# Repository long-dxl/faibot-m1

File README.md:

# Faibot M1

An open mobile robot with two arms and a lifting column, built for university robotics labs. This repository holds its CAD, simulation model, Python SDK, wiring diagrams and assembly guide.

**Status:** design v0.5, before the first engineering build. No physical robot has been assembled yet; everything here is checked in simulation and against the CAD.

## Simulation demos

Three lab tasks, played at 2× speed (60 fps). Each task was measured on 20 randomised seeds before recording.

| Sorting | Pick & place | Opening & closing |
| --- | --- | --- |
|  |  |  |
| Both arms pick at the same time and the base carries the objects to the tray. A zone lock keeps only one arm inside the tray area at a time. [MP4](media/video/m1-sorting-60fps-2x.mp4) · [WebM](media/video/m1-sorting-60fps-2x.webm) | Objects are picked from the table and placed in a box while the base moves between them. [MP4](media/video/m1-pick_place-60fps-2x.mp4) · [WebM](media/video/m1-pick_place-60fps-2x.webm) | The drawer is pulled open, an object is placed inside and the drawer is closed. At the fridge, the right arm opens the door and the left arm takes the can out. [MP4](media/video/m1-open_close-60fps-2x.mp4) · [WebM](media/video/m1-open_close-60fps-2x.webm) |

## What's in this repository

| Folder | What it holds |
| --- | --- |
| [`hardware/`](hardware) | CAD as STEP: the whole robot, one file per part, a parts list and a URDF |
| [`sdk/`](sdk) | The `faibot-m1` Python package and command line: simulation, servo bus, kinematics, teleoperation |
| [`sim/`](sim) | MuJoCo model and meshes, plus a lab scene for pick-and-place tasks |
| [`electrical/`](electrical) | Wiring tables and cable drawings |
| [`product/`](product) | Specification, part register and assembly notes |
| [`docs/vi/`](docs/vi) | Documentation in Vietnamese: specifications, bill of materials, assembly guide |

## Quick start

```
./run.sh              # simulation window with keyboard teleoperation
./run.sh --selftest   # headless check, exit code 0 means it passed
```

The first run creates a virtual environment and installs the dependencies. Python 3.10 or newer is needed. Command-line details are in [`sdk/README.md`](sdk/README.md).

## Robot at a glance

- Two arms, each with six joints and a gripper (6+1, as in the original AM-ARM200), on a lifting column and a three-wheel omni base.
- 18 servos: 7 STS3095 and 11 STS3215, all on 12 V. Wrist yaw servos use IDs 21 and 22.
- Payload per arm (calculated, not measured): peak 2.0 kg at 0.25 m reach, continuous 0 kg at full reach, recommended 0.05 kg or less.
- Base speed up to 0.40 m/s and turn rate up to 0.25 rad/s, with an acceleration ramp that keeps the tip-over margin above 1.5 (static 1.64, dynamic 1.50).

## Platform

Faibotic is building a browser-based platform for this robot: calibration, teleoperation, dataset recording and policy training in one place. It is in development; follow it at [faibotic.com](https://www.faibotic.com).

## Documentation

The written documentation is currently in Vietnamese, starting at [`docs/vi/README.md`](docs/vi/README.md). The hardware and SDK READMEs are in English.

## License

| What | License |
| --- | --- |
| Software (`sdk/`, `scripts/`, `tests/`, `demos/`, `examples/`), the generated MJCF/URDF, and the meshes derived only from AM-ARM200 and MuJoCo Menagerie | [Apache License 2.0](LICENSE) |
| Parts Faibotic drew, as CAD (`cad/`, `hardware/`), as sim meshes (the base, lift carriage and wrist camera meshes in `sim/assets/`) and in `web-assets/m1.glb`; electrical drawings, documentation, images | [CC BY-NC-SA 4.0](LICENSE-hardware). For commercial use, contact founder@faibotic.com |
| Third-party designs in `cad/upstream/`, `hardware/parts/inherited/`, and the third-party parts inside the files above | Apache License 2.0, by their original authors |

The file-by-file list is in [`NOTICE`](NOTICE). Releases v0.5 and earlier published the Faibotic-drawn meshes under the Apache License 2.0. Copyright (c) 2026 Leo Dao (Faibotic). "Faibotic" and "Faibot" are trade names; no trademark rights are granted.

## Credits

The arm and the base frame build on open designs by liyiteng (AM-ARM and AlohaMini), and the servo mesh comes from MuJoCo Menagerie; sources and commits are listed in [`NOTICE`](NOTICE).

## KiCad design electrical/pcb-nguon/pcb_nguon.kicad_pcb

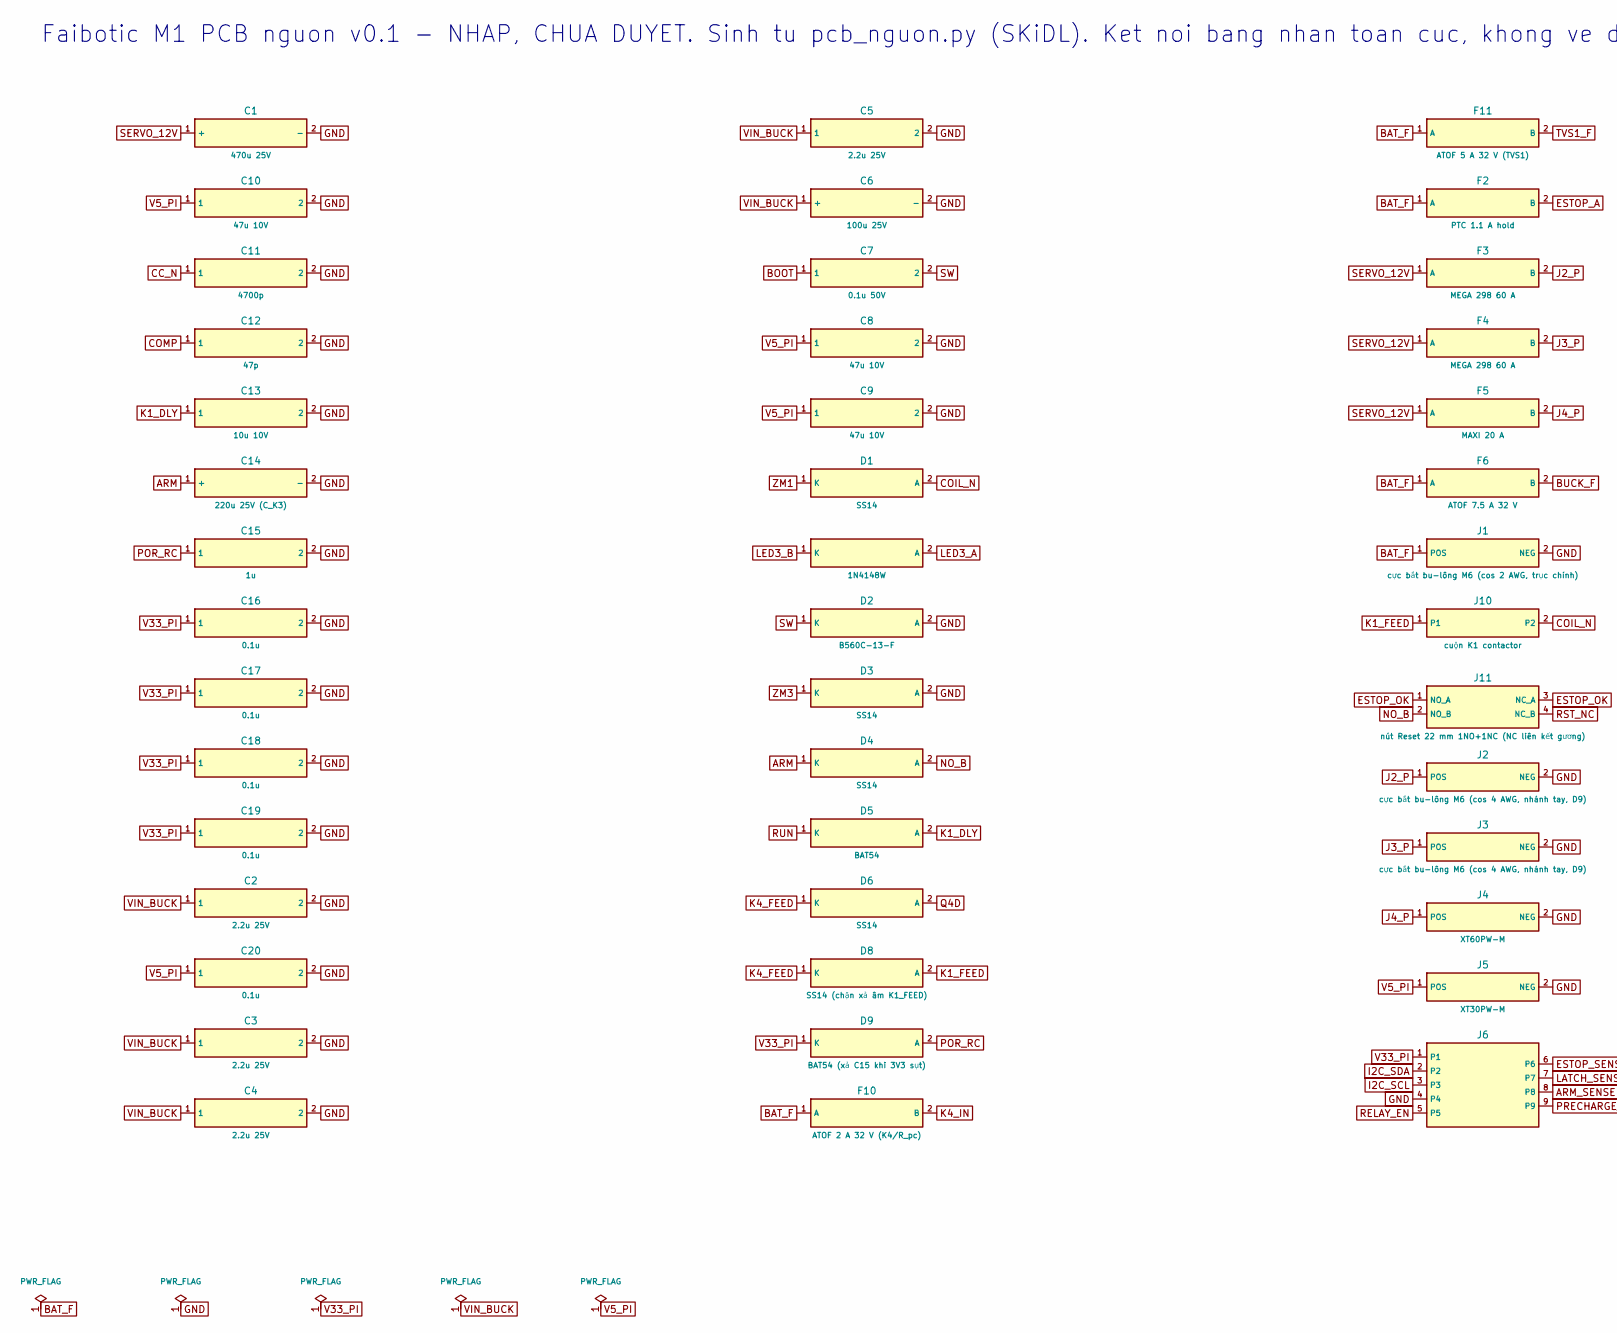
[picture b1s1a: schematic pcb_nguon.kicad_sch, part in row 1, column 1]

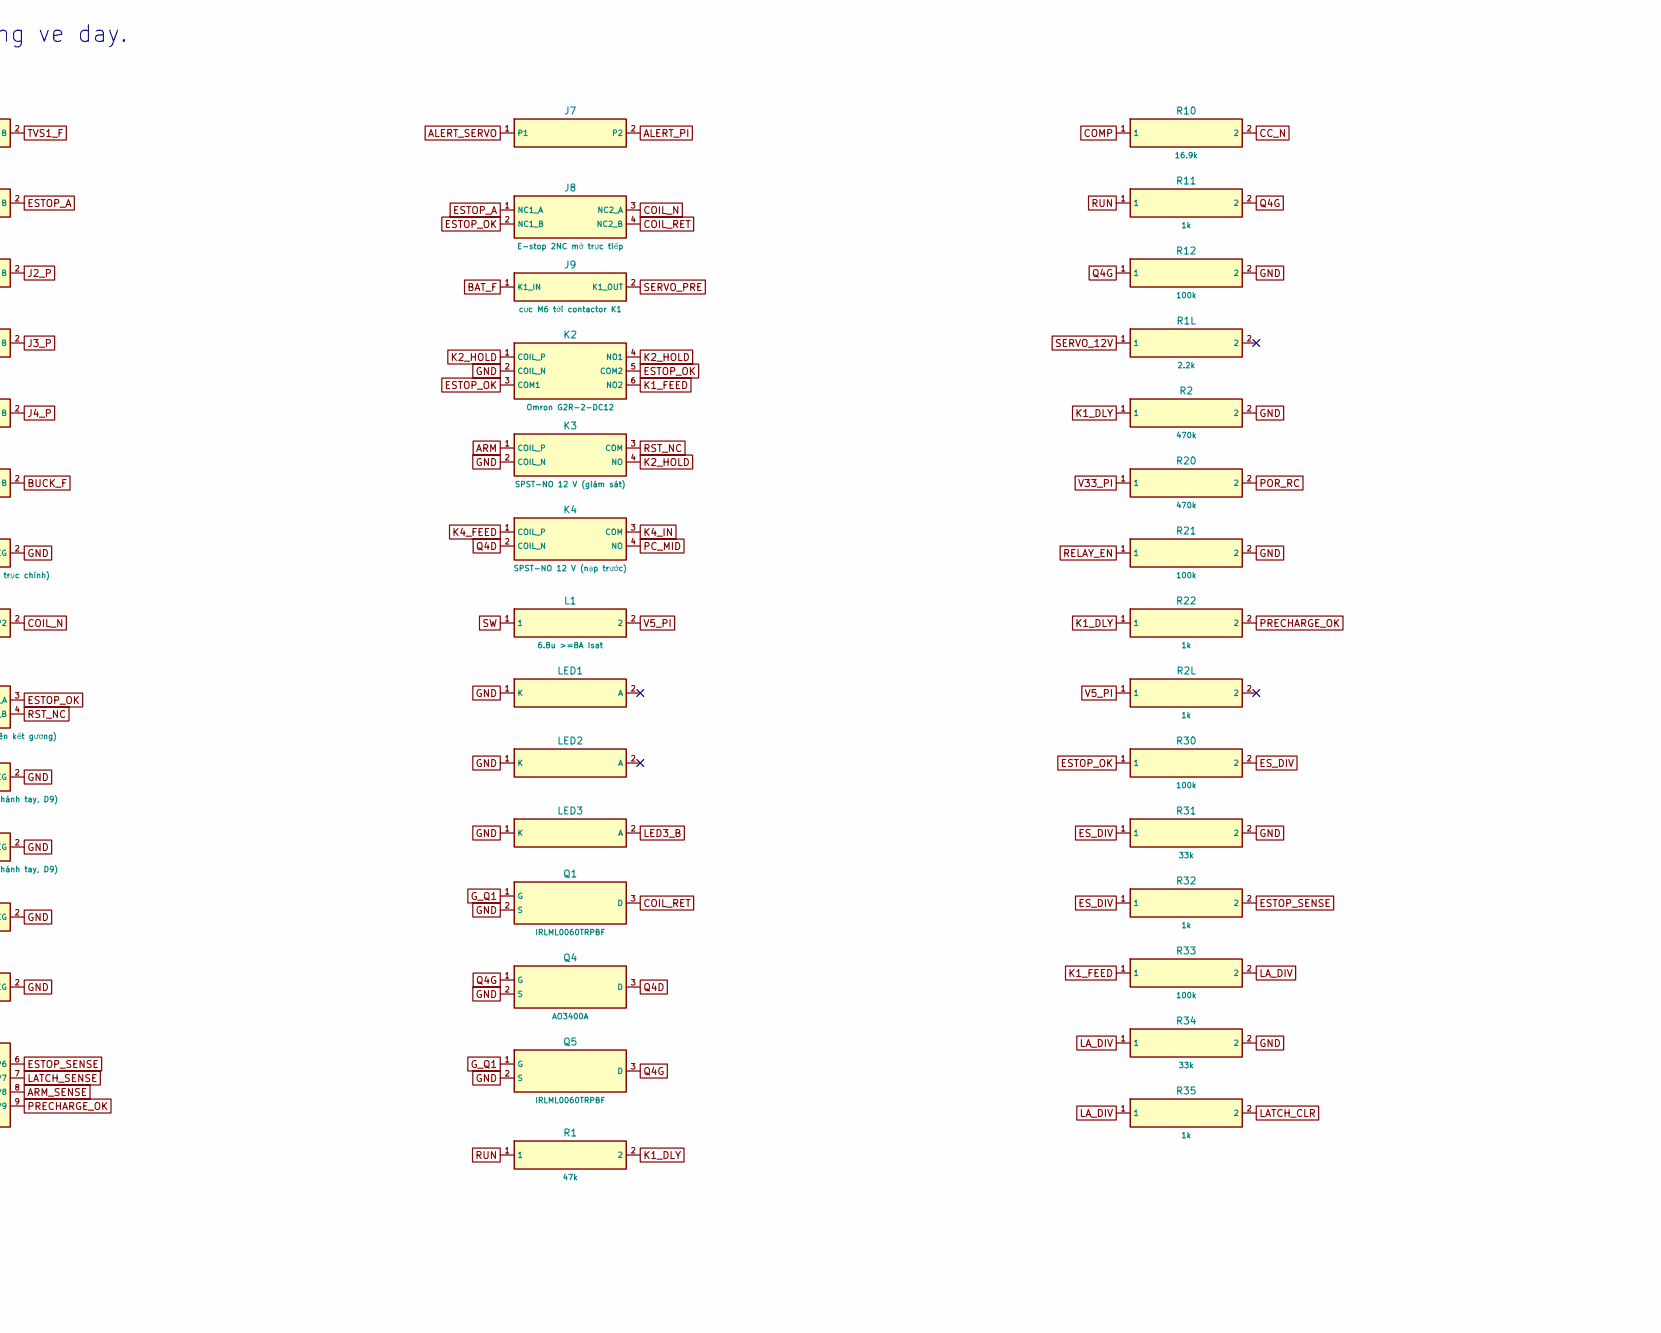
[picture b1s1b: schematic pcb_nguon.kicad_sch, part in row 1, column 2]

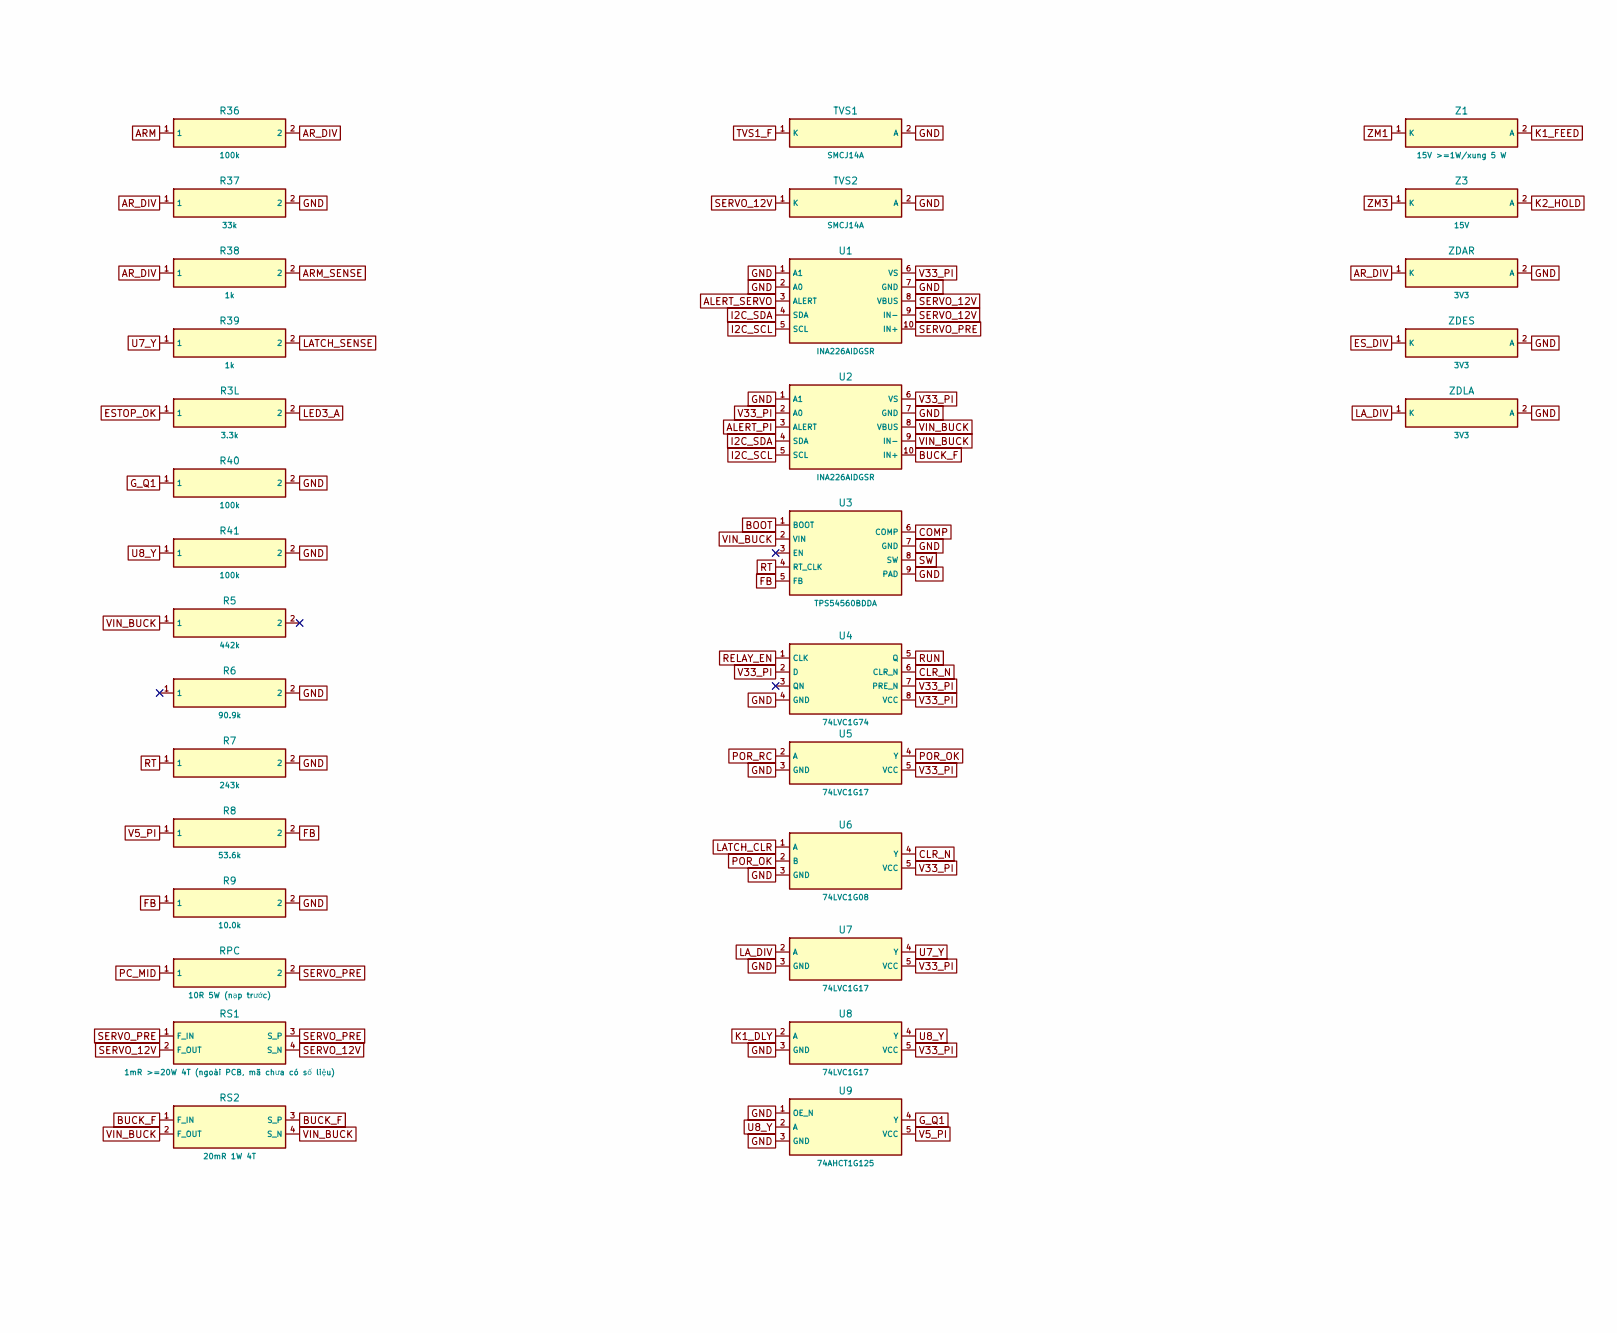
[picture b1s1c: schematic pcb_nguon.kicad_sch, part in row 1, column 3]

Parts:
C1: 470u 25V; CP_Radial
C2, C3, C4, C5: 2.2u 25V; C_0805
C6: 100u 25V; CP_Radial
C7: 0.1u 50V; C_0805
C8, C9, C10: 47u 10V; C_0805
C11: 4700p; C_0805
C12: 47p; C_0805
C13: 10u 10V; C_0805
C14: 220u 25V (C_K3); CP_Radial
C15: 1u; C_0805
C16, C17, C18, C19, C20: 0.1u; C_0805
D1, D3, D4, D6: SS14; D_SMA
D2: B560C-13-F; D_SMA
D5: BAT54; D_SMA
D8: SS14 (chặn xả âm K1_FEED); D_SMA
D9: BAT54 (xả C15 khi 3V3 sụt); D_SMA
F2: PTC 1.1 A hold; Fuse_1812
F3, F4: MEGA 298 60 A; Fuse_Holder
F5: MAXI 20 A; Fuse_Holder
F6: ATOF 7.5 A 32 V; Fuse_Holder
F10: ATOF 2 A 32 V (K4/R_pc); Fuse_Holder
F11: ATOF 5 A 32 V (TVS1); Fuse_Holder
J1: cực bắt bu-lông M6 (cos 2 AWG, trục chính); Terminal_M6_2P
J2, J3: cực bắt bu-lông M6 (cos 4 AWG, nhánh tay, D9); Terminal_M6_2P
J4: XT60PW-M
J5: XT30PW-M
J6: PinHeader_1x09
J7: PinHeader_1x02
J8: E-stop 2NC mở trực tiếp; TerminalBlock_4P_5.08
J9: cực M6 tới contactor K1; Terminal_M6_2P
J10: cuộn K1 contactor; TerminalBlock_2P_5.08
J11: nút Reset 22 mm 1NO+1NC (NC liên kết gương); TerminalBlock_4P_5.08
K2: Omron G2R-2-DC12; Relay_DPDT_G2R
K3: SPST-NO 12 V (giám sát); Relay_SPST_G2R
K4: SPST-NO 12 V (nạp trước); Relay_SPST_G2R
L1: 6.8u >=8A Isat; L_Bourns_SRP1245
LED1, LED2, LED3: LED_0805
Q1, Q5: IRLML0060TRPBF; SOT-23
Q4: AO3400A; SOT-23
R1: 47k; R_0603
R1L: 2.2k; R_0603
R2, R20: 470k; R_0603
R2L, R11, R22, R32, R35, R38, R39: 1k; R_0603
R3L: 3.3k; R_0603
R5: 442k; R_0603
R6: 90.9k; R_0603
R7: 243k; R_0603
R8: 53.6k; R_0603
R9: 10.0k; R_0603
R10: 16.9k; R_0603
R12, R21, R30, R33, R36, R40, R41: 100k; R_0603
R31, R34, R37: 33k; R_0603
RPC: 10R 5W (nạp trước); R_Power_5W
RS1: 1mR >=20W 4T (ngoài PCB, mã chưa có số liệu); Shunt_4T_2512
RS2: 20mR 1W 4T; Shunt_4T_2512
TVS1, TVS2: SMCJ14A; D_SMC
U1, U2: INA226AIDGSR; VSSOP-10
U3: TPS54560BDDA; HSOIC-8_PowerPAD
U4: 74LVC1G74; VSSOP-8
U5, U7, U8: 74LVC1G17; SOT-23-5
U6: 74LVC1G08; SOT-23-5
U9: 74AHCT1G125; SOT-23-5
Z1: 15V >=1W/xung 5 W; D_SOD-123
Z3: 15V; D_SOD-123
ZDAR: 3V3; D_SOD-123
ZDES: 3V3; D_SOD-123
ZDLA: 3V3; D_SOD-123

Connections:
ALERT_PI: J7.2, U2.3 (ALERT)
ALERT_SERVO: J7.1, U1.3 (ALERT)
ARM: C14.1 (+), D4.1 (K), K3.1 (COIL_P), R36.1
ARM_SENSE: J6.8, R38.2
AR_DIV: R36.2, R37.1, R38.1, ZDAR.1 (K)
BAT_F: F2.1 (A), F6.1 (A), F10.1 (A), F11.1 (A), J1.1 (POS), J9.1 (K1_IN)
BOOT: C7.1, U3.1 (BOOT)
BUCK_F: F6.2 (B), RS2.1 (F_IN), RS2.3 (S_P), U2.10 (IN+)
CC_N: C11.1, R10.2
CLR_N: U4.6 (CLR_N), U6.4 (Y)
COIL_N: D1.2 (A), J8.3 (NC2_A), J10.2
COIL_RET: J8.4 (NC2_B), Q1.3 (D)
COMP: C12.1, R10.1, U3.6 (COMP)
ESTOP_A: F2.2 (B), J8.1 (NC1_A)
ESTOP_OK: J8.2 (NC1_B), J11.1 (NO_A), J11.3 (NC_A), K2.3 (COM1), K2.5 (COM2), R3L.1, R30.1
ESTOP_SENSE: J6.6, R32.2
ES_DIV: R30.2, R31.1, R32.1, ZDES.1 (K)
FB: R8.2, R9.1, U3.5 (FB)
GND: C1.2 (-), C2.2, C3.2, C4.2, C5.2, C6.2 (-), C8.2, C9.2, C10.2, C11.2, C12.2, C13.2, C14.2 (-), C15.2, C16.2, C17.2, C18.2, C19.2, C20.2, D2.2 (A), D3.2 (A), J1.2 (NEG), J2.2 (NEG), J3.2 (NEG), J4.2 (NEG), J5.2 (NEG), J6.4, K2.2 (COIL_N), K3.2 (COIL_N), LED1.1 (K), LED2.1 (K), LED3.1 (K), Q1.2 (S), Q4.2 (S), Q5.2 (S), R2.2, R6.2, R7.2, R9.2, R12.2, R21.2, R31.2, R34.2, R37.2, R40.2, R41.2, TVS1.2 (A), TVS2.2 (A), U1.1 (A1), U1.2 (A0), U1.7 (GND), U2.1 (A1), U2.7 (GND), U3.7 (GND), U3.9 (PAD), U4.4 (GND), U5.3 (GND), U6.3 (GND), U7.3 (GND), U8.3 (GND), U9.1 (OE_N), U9.3 (GND), ZDAR.2 (A), ZDES.2 (A), ZDLA.2 (A)
G_Q1: Q1.1 (G), Q5.1 (G), R40.1, U9.4 (Y)
I2C_SCL: J6.3, U1.5 (SCL), U2.5 (SCL)
I2C_SDA: J6.2, U1.4 (SDA), U2.4 (SDA)
J2_P: F3.2 (B), J2.1 (POS)
J3_P: F4.2 (B), J3.1 (POS)
J4_P: F5.2 (B), J4.1 (POS)
K1_DLY: C13.1, D5.2 (A), R1.2, R2.1, R22.1, U8.2 (A)
K1_FEED: D8.2 (A), J10.1, K2.6 (NO2), R33.1, Z1.2 (A)
K2_HOLD: K2.1 (COIL_P), K2.4 (NO1), K3.4 (NO), Z3.2 (A)
K4_FEED: D6.1 (K), D8.1 (K), K4.1 (COIL_P)
K4_IN: F10.2 (B), K4.3 (COM)
LATCH_CLR: R35.2, U6.1 (A)
LATCH_SENSE: J6.7, R39.2
LA_DIV: R33.2, R34.1, R35.1, U7.2 (A), ZDLA.1 (K)
LED3_A: R3L.2
LED3_B: LED3.2 (A)
unnamed: R5.2, R6.1, U3.3 (EN)
unnamed: LED1.2 (A), R1L.2
unnamed: LED2.2 (A), R2L.2
NC_U4_QN: U4.3 (QN)
NO_B: D4.2 (A), J11.2 (NO_B)
PC_MID: K4.4 (NO), RPC.1
POR_OK: U5.4 (Y), U6.2 (B)
POR_RC: C15.1, D9.2 (A), R20.2, U5.2 (A)
PRECHARGE_OK: J6.9, R22.2
Q4D: D6.2 (A), K4.2 (COIL_N), Q4.3 (D)
Q4G: Q4.1 (G), Q5.3 (D), R11.2, R12.1
RELAY_EN: J6.5, R21.1, U4.1 (CLK)
RST_NC: J11.4 (NC_B), K3.3 (COM)
RT: R7.1, U3.4 (RT_CLK)
RUN: D5.1 (K), R1.1, R11.1, U4.5 (Q)
SERVO_12V: C1.1 (+), F3.1 (A), F4.1 (A), F5.1 (A), R1L.1, RS1.2 (F_OUT), RS1.4 (S_N), TVS2.1 (K), U1.8 (VBUS), U1.9 (IN-)
SERVO_PRE: J9.2 (K1_OUT), RPC.2, RS1.1 (F_IN), RS1.3 (S_P), U1.10 (IN+)
SW: C7.2, D2.1 (K), L1.1, U3.8 (SW)
TVS1_F: F11.2 (B), TVS1.1 (K)
U7_Y: R39.1, U7.4 (Y)
U8_Y: R41.1, U8.4 (Y), U9.2 (A)
V5_PI: C8.1, C9.1, C10.1, C20.1, J5.1 (POS), L1.2, R2L.1, R8.1, U9.5 (VCC)
V33_PI: C16.1, C17.1, C18.1, C19.1, D9.1 (K), J6.1, R20.1, U1.6 (VS), U2.2 (A0), U2.6 (VS), U4.2 (D), U4.7 (PRE_N), U4.8 (VCC), U5.5 (VCC), U6.5 (VCC), U7.5 (VCC), U8.5 (VCC)
VIN_BUCK: C2.1, C3.1, C4.1, C5.1, C6.1 (+), R5.1, RS2.2 (F_OUT), RS2.4 (S_N), U2.8 (VBUS), U2.9 (IN-), U3.2 (VIN)
ZM1: D1.1 (K), Z1.1 (K)
ZM3: D3.1 (K), Z3.1 (K)

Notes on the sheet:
Faibotic M1 PCB nguon v0.1 - NHAP, CHUA DUYET. Sinh tu pcb_nguon.py (SKiDL). Ket noi bang nhan toan cuc, khong ve day.

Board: 2 copper layers, 103 parts (0 on the bottom side), 58 nets, no tracks yet.

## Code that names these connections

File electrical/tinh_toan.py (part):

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 ("W12","Sac 12,6 V","BMS P+/P- (cong sac)",14,0.30,3.0,5.0,"XT60","bo sac 3S 12,6 V [chua chon]; dung truoc D0 va F1",5,"ATOF 5 A sat cong sac"),
 ("W13","pin 3S5P","BMS balance",24,0.10,0.05,0.2,"JST-XH 4P","day can bang",1,"1 A nhanh tren moi tap"),
 ("W14","PCB J8","nut E-stop 2NC",22,0.50,0.50,0.8,"cos tron / vit","vong cuon K1 0,46 A + K2 0,04 + LED/chia ap; PTC F2 1,1 A hold; Imax/Isc cua PTC F2: khong chot (chuoi A, da thay) (N9, can datasheet)",1.1,"PTC F2 1,1 A hold"),
 ("W15","PCB J6/J7","Pi 5 GPIO/I2C",26,0.20,0.01,0.1,"Dupont 2,54","3V3, SDA, SCL, GND, RELAY_EN, ESTOP/LATCH/ARM_SENSE, PRECHARGE_OK, ALERT",0,"khong (Pi gioi han)"),
 ("W16","PCB J9","contactor K1 200 A (vao + ra)",4,0.30,I_trunk,Ipk_trunk,"cos M6 bu-long","2 chang J9 <-> K1; tong 0,30 m",60,"F1 MEGA 60 A"),
 ("W17","PCB J11","nut Reset 1NO+1NC (4 day)",22,0.50,0.03,0.05,"vit","dong ESTOP_OK -> K3/K2, ~0,03 A",1.1,"PTC F2 1,1 A hold"),
 ("W18","PCB J10","cuon K1 contactor",22,0.30,0.46,0.5,"vit","cuon 5,5 W, ~0,46 A",1.1,"PTC F2 1,1 A hold"),
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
